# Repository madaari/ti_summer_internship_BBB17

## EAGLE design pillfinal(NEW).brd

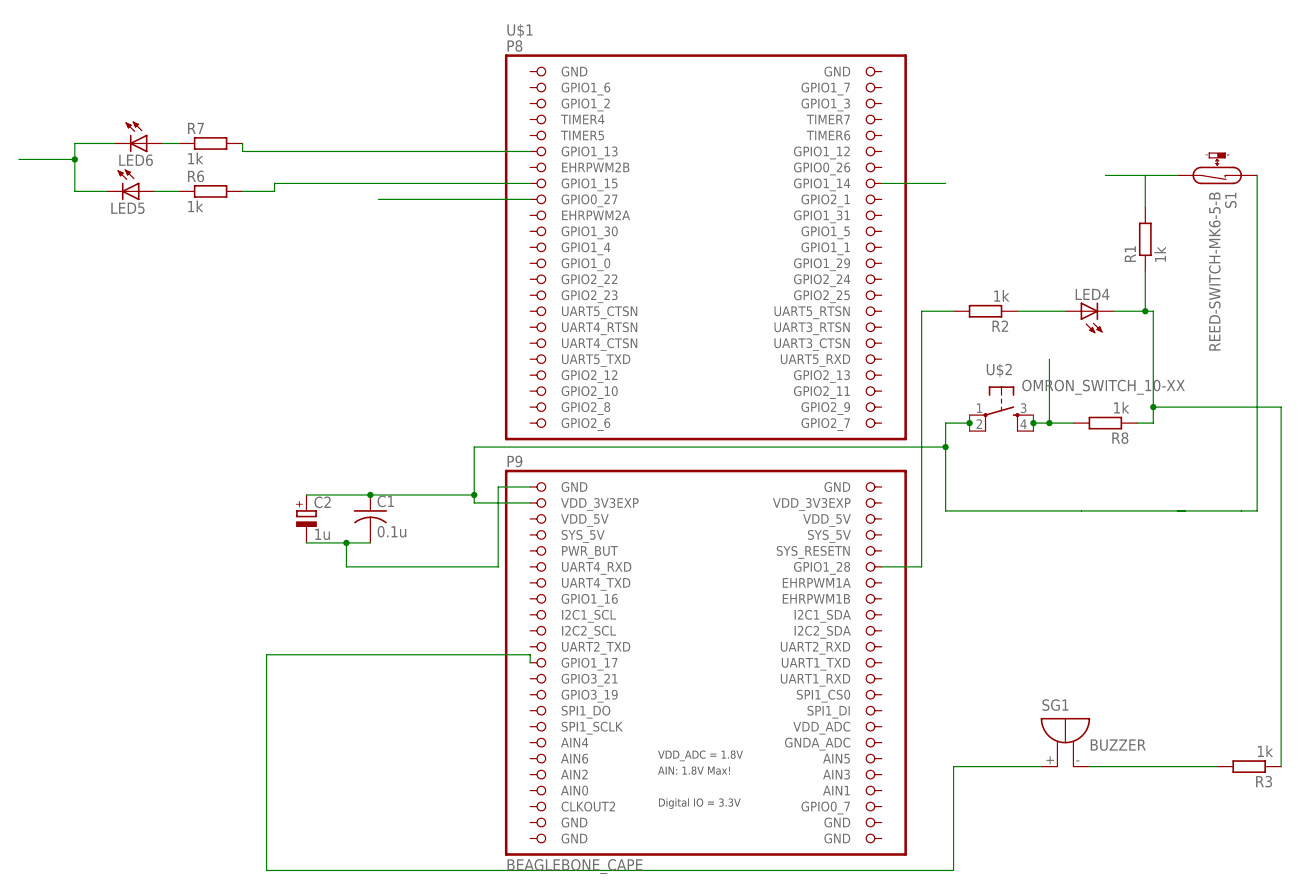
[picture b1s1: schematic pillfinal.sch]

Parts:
C1: 0.1u; C0805
C2: 1u; CT3528
LED4, LED5, LED6: LEDCHIPLED_0805; CHIPLED_0805
R1, R2, R3, R6, R7, R8: 1k; R0805
S1: REED-SWITCH-MK6-5-B; MK6-5
SG1: BUZZER; F/TMB
U$1: BEAGLEBONE_CAPE
U$2: OMRON_SWITCH_10-XX; B3F-10XX

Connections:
3.3V: C1.1, C2.- (+), S1.1, U$1.49 (VDD_3V3EXP), U$2.1, U$2.2 (P1)
GND: C1.2, C2.+ (-), LED4.C, LED5.C, LED6.C, R1.1, R3.1, R8.1, U$1.1 (GND), U$1.2 (GND), U$1.47 (GND), U$1.48 (GND), U$1.89 (GND), U$1.90 (GND), U$1.91 (GND), U$1.92 (GND)
GNDA_ADC: U$1.80 (GNDA_ADC)
LED1: R7.2, U$1.11 (GPIO1_13)
LED2: R6.2, U$1.15 (GPIO1_15)
LED3: R2.2, U$1.58 (GPIO1_28)
unnamed: LED4.A, R2.1
unnamed: R3.2, SG1.-
unnamed: LED5.A, R6.1
unnamed: LED6.A, R7.1
unnamed: SG1.+, U$1.69 (GPIO1_17)
P9: R8.2, U$1.16 (GPIO1_14), U$2.3 (S), U$2.4 (S1)
REED: R1.2, S1.2, U$1.17 (GPIO0_27)
SYS_5V: U$1.53 (SYS_5V), U$1.54 (SYS_5V)
VDD_3V3EXP: U$1.50 (VDD_3V3EXP)
VDD_5V: U$1.51 (VDD_5V), U$1.52 (VDD_5V)
VDD_ADC: U$1.78 (VDD_ADC)

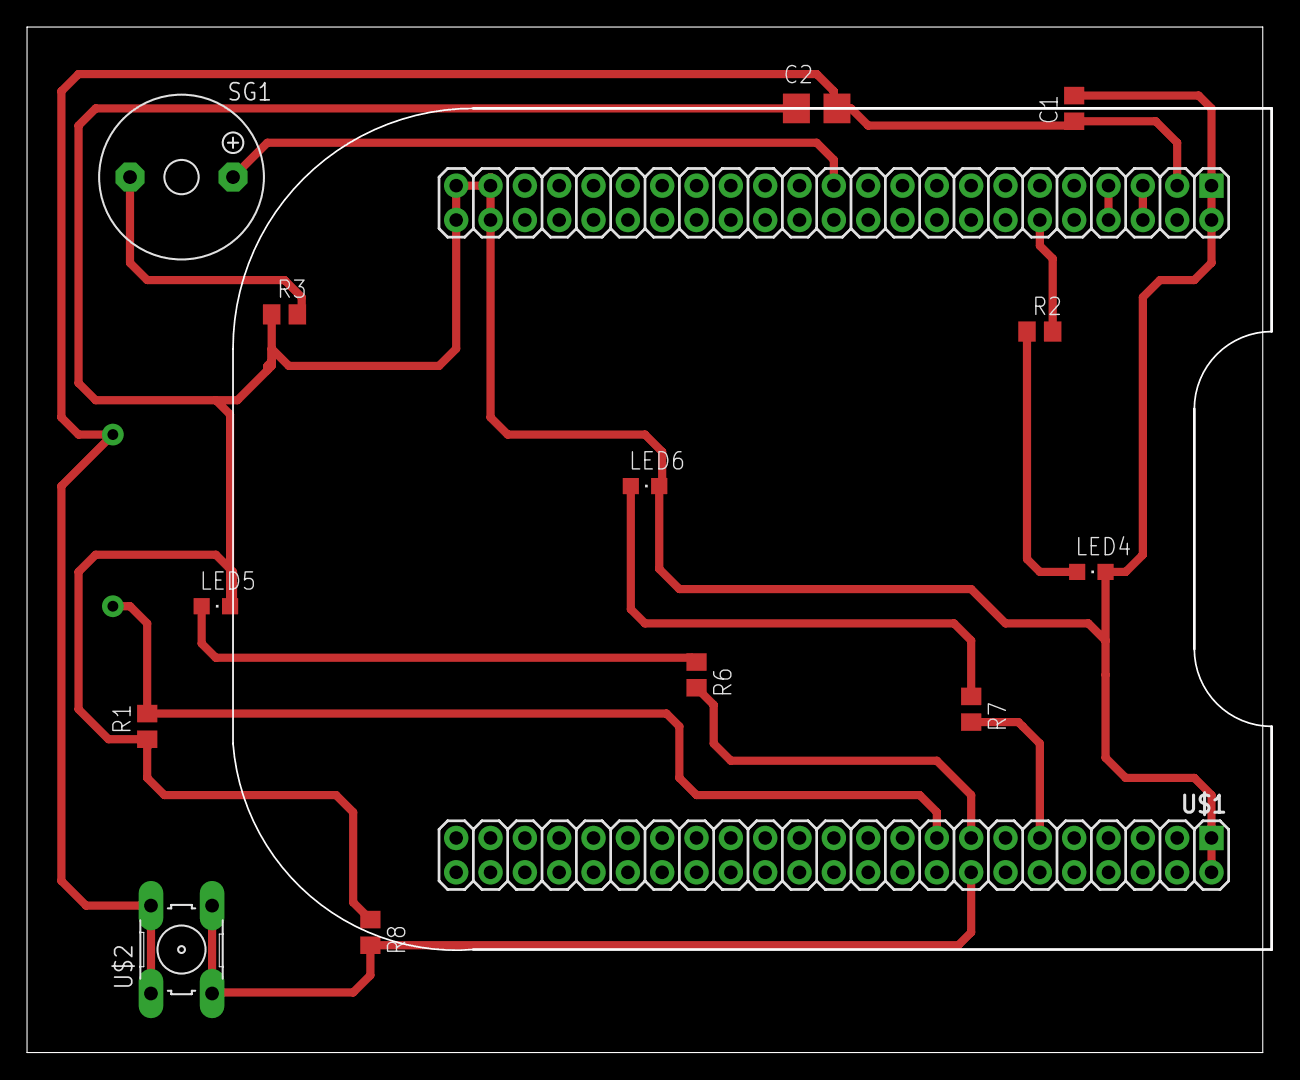
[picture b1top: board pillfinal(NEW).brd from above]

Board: 2 copper layers, 92.0 x 75.7 mm, 15 parts (1 on the bottom side), 14 nets.

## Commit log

2017-06-27 Added PWM header files
2017-06-28 Added PWM for pin 16
2017-06-28 Add files via upload
    edit project files
2017-06-28 Rename pillboxfinal.py to AMPILL/pillboxfinal.py
2017-06-28 Rename pillfinal(NEW).brd to AMPILL/pillfinal.brd
2017-06-28 Rename pillfinal(NEW).sch to AMPILL/pillfinal.sch
2017-06-29 Added Project content
2017-07-25 Added working speech recognition on BBB
